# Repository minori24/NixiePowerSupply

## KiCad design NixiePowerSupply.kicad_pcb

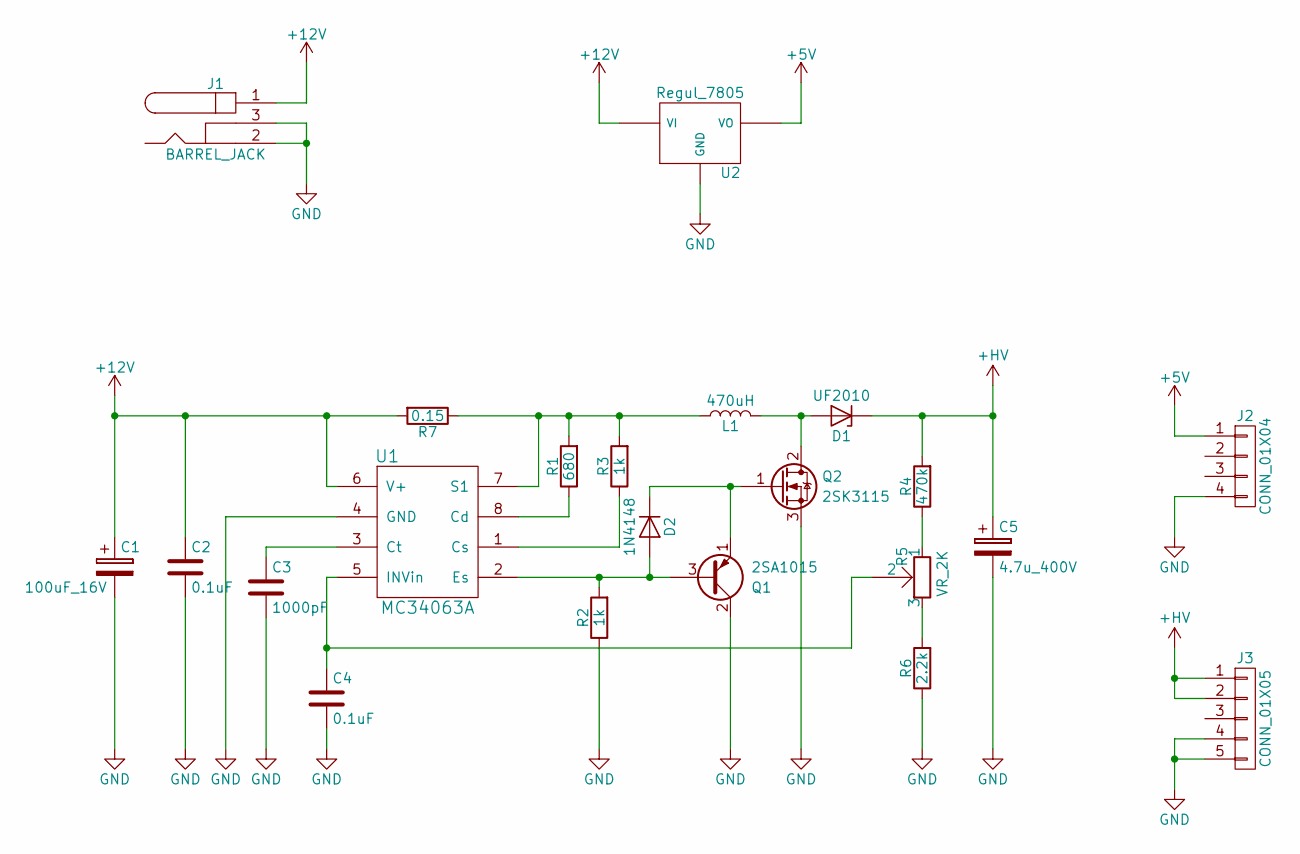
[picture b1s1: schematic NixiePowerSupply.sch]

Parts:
C1: 100uF_16V; CP_Radial_D6.3mm_P2.50mm
C2, C4: 0.1uF; C_Disc_D5.0mm_W2.5mm_P2.50mm
C3: 1000pF; C_Disc_D5.0mm_W2.5mm_P5.00mm
C5: 4.7u_400V; CP_Radial_D10.0mm_P5.00mm
D1: UF2010; D_DO-15_P5.08mm_Vertical_AnodeUp
D2: 1N4148; D_DO-35_SOD27_P7.62mm_Horizontal
J1: BARREL_JACK
J2: CONN_01X04; Pin_Header_Straight_1x04_Pitch2.54mm
J3: CONN_01X05; Pin_Header_Straight_1x05_Pitch2.54mm
L1: 470uH; Inductors_LHL13NB471K
Q1: 2SA1015; TO-92_Inline_Narrow_Oval
Q2: 2SK3115; TO-220-3_Vertical
R1: 680; R_Axial_DIN0309_L9.0mm_D3.2mm_P12.70mm_Horizontal
R2, R3: 1k; R_Axial_DIN0207_L6.3mm_D2.5mm_P10.16mm_Horizontal
R4: 470k; R_Axial_DIN0207_L6.3mm_D2.5mm_P10.16mm_Horizontal
R5: VR_2K; VOL_3362P-1-202LF
R6: 2.2k; R_Axial_DIN0207_L6.3mm_D2.5mm_P10.16mm_Horizontal
R7: 0.15; R_Axial_DIN0414_L11.9mm_D4.5mm_P15.24mm_Horizontal
U1: MC34063A; DIP-8_W7.62mm
U2: Regul_7805; TO-220-3_Vertical

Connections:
+5V: J2.1, U2.3 (VO)
+12V: C1.1, C2.1, J1.1, R7.2, U1.6 (V+), U2.1 (VI)
+HV: C5.1, D1.1 (K), J3.1, J3.2, R4.2
GND: C1.2, C2.2, C3.2, C4.2, C5.2, J1.2, J1.3, J2.4, J3.4, J3.5, Q1.2 (C), Q2.3 (S), R2.1, R6.1, U1.4 (GND), U2.2 (GND)
unnamed: C3.1, U1.3 (Ct)
unnamed: C4.1, R5.2, U1.5 (INVin)
unnamed: D1.2 (A), L1.2, Q2.2 (D)
unnamed: D2.1 (K), Q1.1 (E), Q2.1 (G)
unnamed: D2.2 (A), Q1.3 (B), R2.2, U1.2 (Es)
unnamed: L1.1, R1.2, R3.2, R7.1, U1.7 (S1)
unnamed: R1.1, U1.8 (Cd)
unnamed: R3.1, U1.1 (Cs)
unnamed: R4.1, R5.1
unnamed: R5.3, R6.2

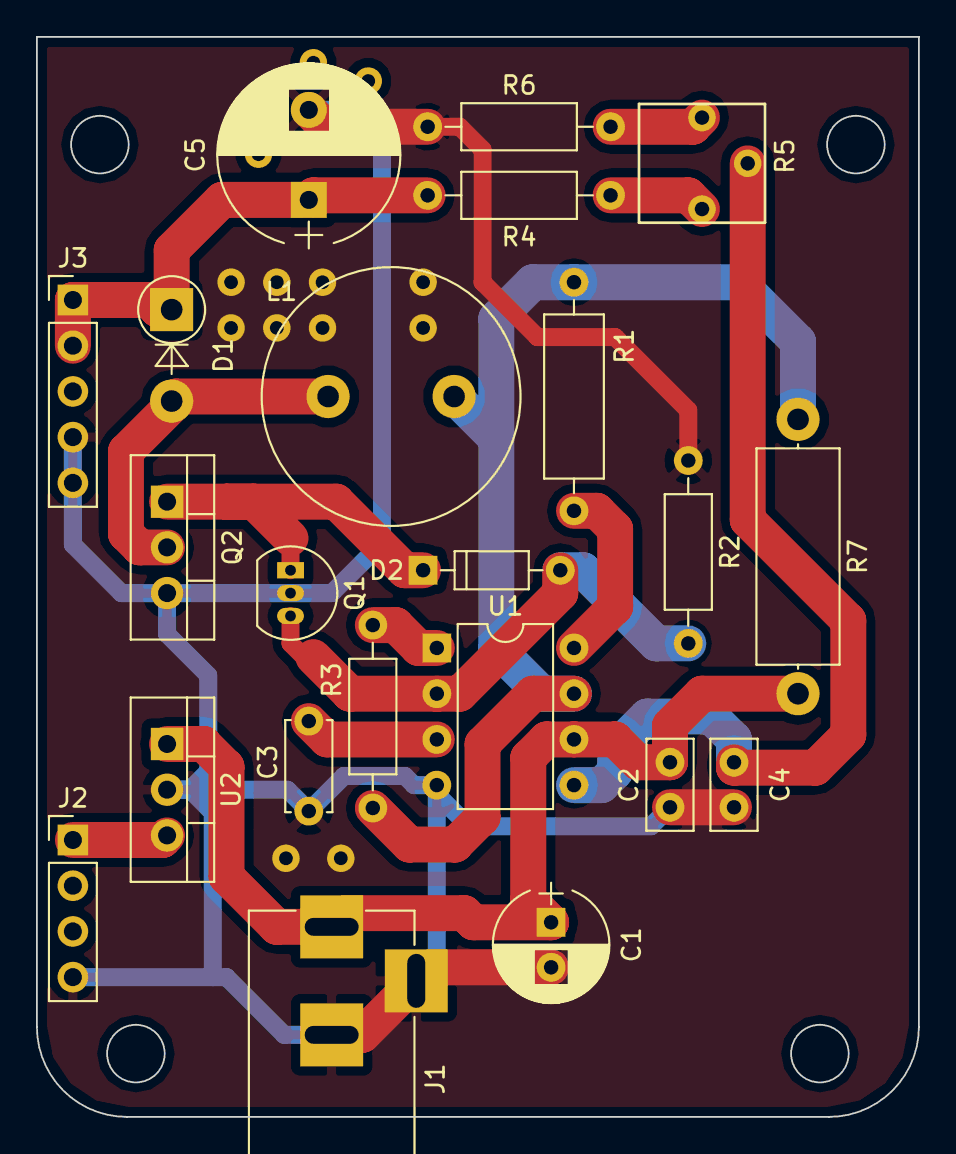
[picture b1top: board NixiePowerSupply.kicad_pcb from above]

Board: 2 copper layers, 49.0 x 60.0 mm, 22 parts (0 on the bottom side), 14 nets.

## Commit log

2017-10-10 Base schematics comp
2017-10-11 Add costed BOM
2017-10-12 Modify cap footprint
2017-10-12 parts moved for layout chnge
2017-10-18 Placement & Trace layoit done
2017-10-23 first gerber out
